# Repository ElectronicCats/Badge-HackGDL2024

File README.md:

# Badge Hack GDL 2024
Inspirado en la piñata mas famosa del Guadalajara este es el badge electronico de [HackGDL](https://hackgdl.net/)

## Características

- Microcontrolador Puya PY32F002AA15M6TU
- Baterias CR2030
- 4 LEDs SMD

# Firmware
- Para hacer cambios en el firmware revisar el [README](https://github.com/ElectronicCats/Badge-HackGDL2024/tree/main/firmware#readme)

## License

Diseñado por Electronic Cats para HackGDL

Electronic Cats invests time and resources in providing this open-source design. Please support Electronic Cats and open-source hardware by purchasing products from Electronic Cats!

Hardware released under

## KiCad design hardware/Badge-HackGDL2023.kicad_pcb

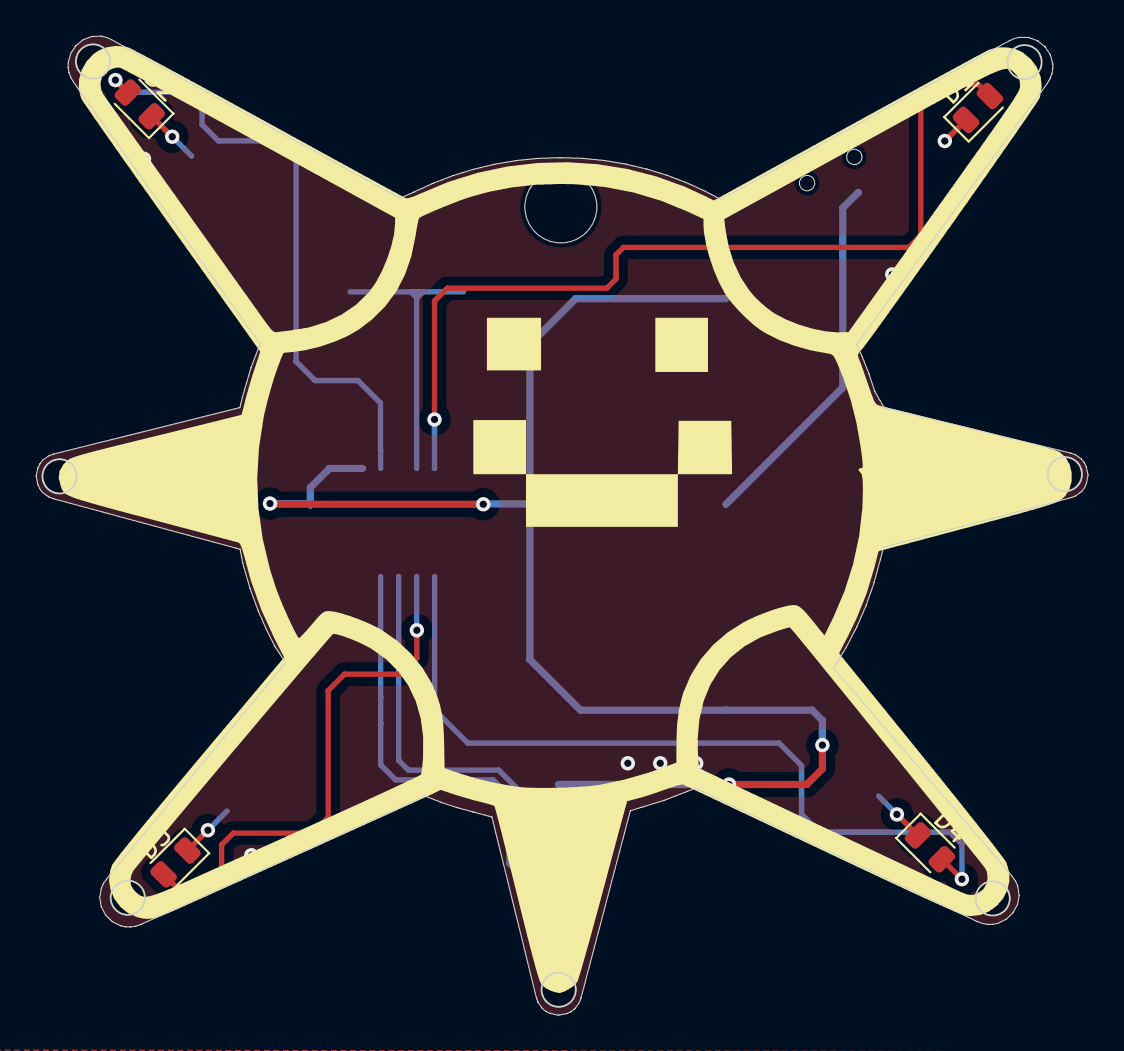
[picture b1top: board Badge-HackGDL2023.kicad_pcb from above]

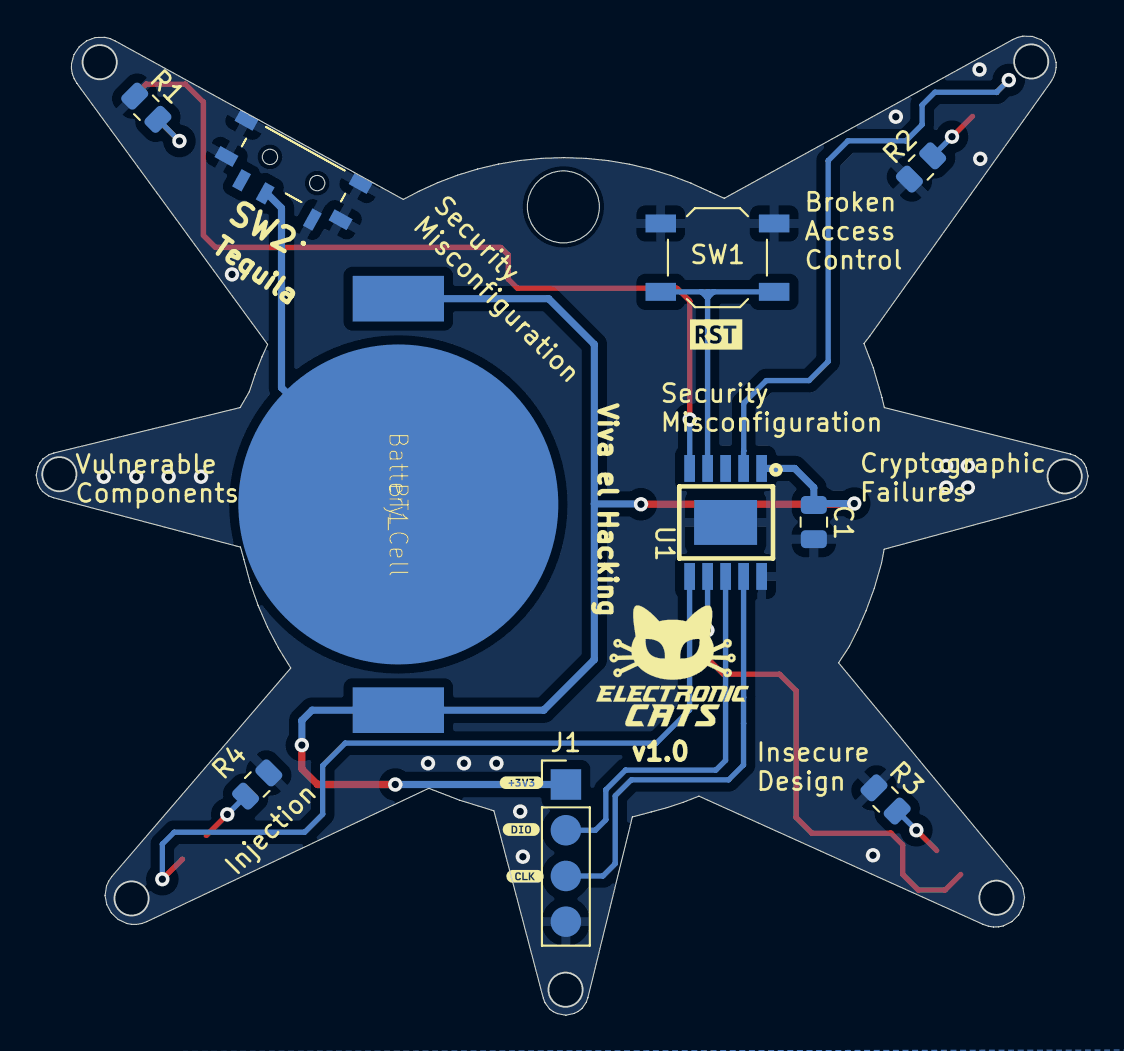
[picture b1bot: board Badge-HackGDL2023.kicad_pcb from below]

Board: 2 copper layers, 58.4 x 54.3 mm, 18 parts (14 on the bottom side), 14 nets.

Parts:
BT1: Battery_Cell; BAT-HLD-001
C1: 0.1uF; C_0805_2012Metric
D1: Blue; LED_0805_2012Metric
D2: Green; LED_0805_2012Metric
D3: Red; LED_0805_2012Metric
D4: Yellow; LED_0805_2012Metric
J1: SWD; PinHeader_1x04_P2.54mm_Vertical
R1, R2, R3, R4: 330R; R_0805_2012Metric
SW1: SW_RST; SW_SPST_TL3342
SW2: On; MSK12C02
U1: PY32F002AA15M6TU; PY32F002AA15M
kibuzzard-65BC4D69: G***; kibuzzard-65BC4D69
kibuzzard-65BC4D87: G***; kibuzzard-65BC4D87
kibuzzard-65BC4E20: G***; kibuzzard-65BC4E20
kibuzzard-65BD0189: G***; kibuzzard-65BD0189

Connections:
+3.3V: BT1.2 (+), C1.1, J1.1, U1.1 (VCC)
/NRST: SW1.2, U1.4 (PA0/PF2-NRST)
/PA1: D1.2 (A), U1.5 (PA1)
/PA6: D4.2 (A), U1.6 (PA6)
/PA7: D3.2 (A), U1.7 (PA7)
/PF0: D2.2 (A), U1.2 (PF0-OSCIN)
/SWCLK: J1.3, U1.9 (PA14-SWC/PB3)
/SWDIO: J1.2, U1.8 (PA13-SWD)
GND: C1.2, J1.4, R1.1, R2.1, R3.1, R4.1, SW1.1, SW2.1 (A), SW2.4 (C), U1.10 (GND)
unnamed: BT1.1 (-), SW2.2 (B)
unnamed: D1.1 (K), R1.2
unnamed: D2.1 (K), R2.2
unnamed: D3.1 (K), R3.2
unnamed: D4.1 (K), R4.2

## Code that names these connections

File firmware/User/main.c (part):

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void circleSequence()
{
  // HAL_Delay(delay);
  HAL_GPIO_OnPin(GPIOF, GPIO_PIN_0); // Start with PF0 ON
  HAL_Delay(delay);
  HAL_GPIO_OffPin(GPIOF, GPIO_PIN_0);
  HAL_GPIO_OnPin(GPIOA, GPIO_PIN_1);
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  HAL_GPIO_OffPin(GPIOA, GPIO_PIN_6);
  HAL_GPIO_OnPin(GPIOA, GPIO_PIN_7);
  HAL_Delay(delay);
  HAL_GPIO_OffPin(GPIOA, GPIO_PIN_7); // Turn off PA7
  // Return
  HAL_GPIO_OnPin(GPIOF, GPIO_PIN_0); // Start with PF0
  HAL_Delay(delay);
  HAL_GPIO_OffPin(GPIOF, GPIO_PIN_0);
  HAL_GPIO_OnPin(GPIOA, GPIO_PIN_7);
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// Sequence 2
void crossSequence()
{
  HAL_GPIO_OnPin(GPIOF, GPIO_PIN_0); // Start with PF0
  HAL_Delay(delay);
  HAL_GPIO_OffPin(GPIOF, GPIO_PIN_0);
  HAL_GPIO_OnPin(GPIOA, GPIO_PIN_6);
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  HAL_GPIO_OffPin(GPIOA, GPIO_PIN_1);
  HAL_GPIO_OnPin(GPIOA, GPIO_PIN_7);
  HAL_Delay(delay);
  HAL_GPIO_OffPin(GPIOA, GPIO_PIN_7); // Turn off PA7
  HAL_Delay(delay);
}

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// Seqeuence 3
void crossSequence2()
{
  HAL_GPIO_OnPin(GPIOF, GPIO_PIN_0); // Start with PF0
  HAL_GPIO_OnPin(GPIOA, GPIO_PIN_6); // Start with PA6
  HAL_Delay(delay2);
  HAL_GPIO_OffPin(GPIOF, GPIO_PIN_0);
  HAL_GPIO_OffPin(GPIOA, GPIO_PIN_6);
  HAL_GPIO_OnPin(GPIOA, GPIO_PIN_1);
  HAL_GPIO_OnPin(GPIOA, GPIO_PIN_7);
  HAL_Delay(delay2);
  HAL_GPIO_OffPin(GPIOA, GPIO_PIN_1); // Turn down PA1
  HAL_GPIO_OffPin(GPIOA, GPIO_PIN_7); // Turn down PA7
}
// Seqeuence 4

void continuosCircleSequence()
{
  HAL_GPIO_OnPin(GPIOF, GPIO_PIN_0); // Start with PF0
  HAL_GPIO_OnPin(GPIOA, GPIO_PIN_1); // Start with PA6
  HAL_Delay(delay);
  HAL_GPIO_OffPin(GPIOF, GPIO_PIN_0);
  HAL_GPIO_OnPin(GPIOA, GPIO_PIN_6);
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  HAL_GPIO_OffPin(GPIOA, GPIO_PIN_1);
  HAL_GPIO_OnPin(GPIOA, GPIO_PIN_7);
  HAL_Delay(delay);
  HAL_GPIO_OffPin(GPIOA, GPIO_PIN_6); // Turn down PA1
  HAL_GPIO_OnPin(GPIOF, GPIO_PIN_0);
  HAL_Delay(delay);
  HAL_GPIO_OffPin(GPIOA, GPIO_PIN_7);
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  HAL_GPIO_OffPin(GPIOA, GPIO_PIN_7);
  HAL_GPIO_OnPin(GPIOA, GPIO_PIN_6); // 123
  HAL_Delay(delay);
  HAL_GPIO_OffPin(GPIOF, GPIO_PIN_0); // Turn off PF0
  HAL_GPIO_OnPin(GPIOA, GPIO_PIN_7);  // 234
  HAL_Delay(delay);
  HAL_GPIO_OffPin(GPIOA, GPIO_PIN_1); // Turn off PA1
  HAL_GPIO_OnPin(GPIOF, GPIO_PIN_0);  // 341
  HAL_Delay(delay);
  HAL_GPIO_OffPin(GPIOA, GPIO_PIN_6); // Turn off PA6
  HAL_GPIO_OnPin(GPIOA, GPIO_PIN_1);  // 412
  HAL_Delay(delay);
  /*
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
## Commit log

2024-02-02 Schematic and PCB started
2024-02-02 add first edge cuts
2024-02-02 Update routing
2024-02-02 Update BOM
2024-02-02 update labels
2024-02-12 LED's Firmware with 7 different sequences
2024-02-12 Firmware's readme added
2024-02-14 message
2024-02-15 Update Sequences and last sequences added
2024-02-20 Code Optimization
2024-02-28 fix: infinite loop added
2024-03-19 fix(hw): rename files

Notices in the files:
firmware/User/main.c:
© Copyright (c) Puya Semiconductor Co.
All rights reserved.
© Copyright (c) 2016 STMicroelectronics.
This software component is licensed by ST under BSD 3-Clause license,
the "License"; You may not use this file except in compliance with the
License. You may obtain a copy of the License at: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
(C) COPYRIGHT Puya *****END OF FILE
